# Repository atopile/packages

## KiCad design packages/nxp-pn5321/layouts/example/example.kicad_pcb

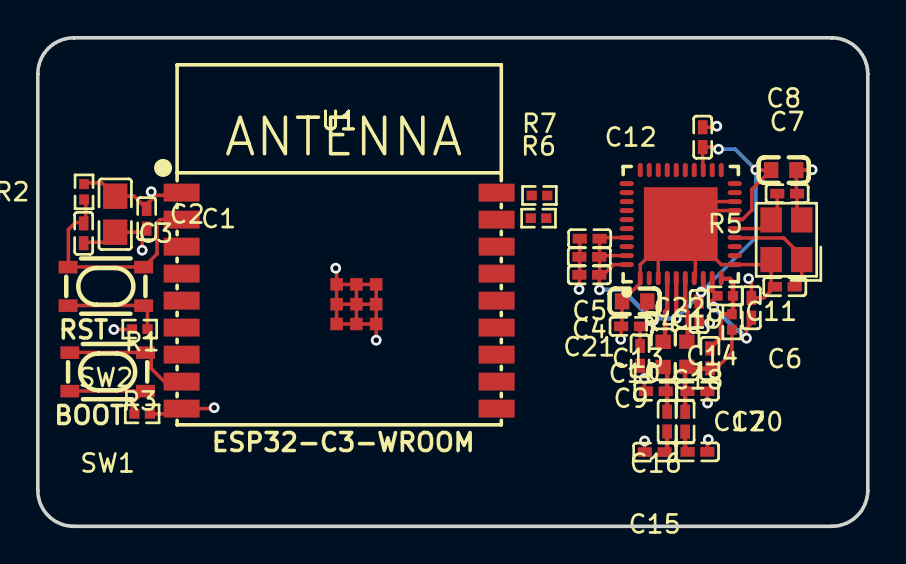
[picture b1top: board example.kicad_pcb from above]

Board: 2 copper layers, 46.1 x 27.1 mm, 36 parts (0 on the bottom side), 19 nets.

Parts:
C1, C4, C5, C9, C11, C12, C13, C14, C17, C20, C21, C22: 100nF ±10% 16V X7R; C0402
C2: 10µF ±10% 16V X5R; C0805
C3: 1µF ±10% 25V X5R; C0402
C6, C7: 20pF ±5% 50V C0G; C0402
C8, C10: 10µF ±20% 6.3V X5R; C0603
C15, C18: 100pF ±5% 50V C0G; C0402
C16, C19: 220pF ±10% 50V X7R; C0402
L1, L2: IND-SMD_L1.6-W0.8-1
R1, R3: 100Ω ±1% 62.5mW; R0402
R2: 10kΩ ±1% 62.5mW; R0402
R4, R5: 1kΩ ±1% 62.5mW; R0402
R6, R7: 4.7kΩ ±1% 62.5mW; R0402
SW1, SW2: KEY-SMD_4P-L4.2-W3.2-P2.20-LS4.6
U1: BULETM-SMD_ESPRESSIF_ESP32-C3-WROOM-02-N4-4MB
U2: QFN-40_L6.0-W6.0-P0.50-BL-EP4.1
X1: CRYSTAL-SMD_4P-L3.2-W2.5-BL

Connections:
-line-0: C18.1, C20.2
-line-1: C15.1, C17.2
MOSI_SDA_HSU_TX: R7.1, U1.18, U2.28
NSS_P50_SCL_HSU_RX: R6.1, U1.17, U2.27
RSTOUT_N: U1.10, U2.26
RX: C13.2, R4.2, R5.2, U2.10
TX1: L1.2, U2.4
TX2: L2.2, U2.6
VMID: C22.1, R5.1, U2.9
gnd: C1.2, C2.2, C3.2, C4.2, C5.2, C6.2, C7.2, C8.2, C9.2, C10.2, C11.2, C12.2, C14.2, C15.2, C16.2, C18.2, C19.2, C21.2, C22.2, R1.2, R3.2, U1.9, U1.19, U2.1, U2.3, U2.7, U2.11, U2.17, U2.18, U2.41, X1.2, X1.4
hv: C1.1, C2.1, C4.1, C5.1, C8.1, C9.1, C10.1, C11.1, C12.1, C14.1, C21.1, R2.2, R6.2, R7.2, U1.1, U2.5, U2.8, U2.16, U2.23, U2.37, U2.39, U2.40
input-0: R1.1, SW1.1, SW1.2
input-1: R3.1, SW2.1, SW2.2
nfc-input: C6.1, U2.14, X1.1
nfc-output: C7.1, U2.15, X1.3
output-0: SW1.3, SW1.4, U1.8
output-1: C3.1, R2.1, SW2.3, SW2.4, U1.2
tx_1_mid: C16.1, C17.1, L1.1
tx_2_mid: C13.1, C19.1, C20.1, L2.1, R4.1

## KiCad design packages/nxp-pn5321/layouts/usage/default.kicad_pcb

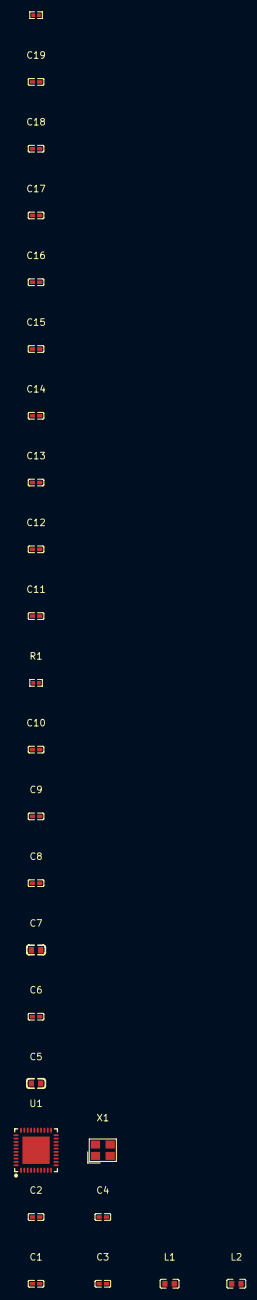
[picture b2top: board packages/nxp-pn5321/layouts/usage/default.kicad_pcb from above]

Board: 2 copper layers, 25 parts (0 on the bottom side), 12 nets.

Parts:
C1, C2, C6, C8, C9, C10, C11, C14, C17, C18, C19: 100nF ±10% 16V X7R; C0402
C3, C4: 20pF ±5% 50V C0G; C0402
C5, C7: 10µF ±20% 6.3V X5R; C0603
C12, C15: 100pF ±5% 50V C0G; C0402
C13, C16: 220pF ±10% 50V X7R; C0402
L1, L2: IND-SMD_L1.6-W0.8-1
R1, R2: 1kΩ ±1% 62.5mW; R0402
U1: QFN-40_L6.0-W6.0-P0.50-BL-EP4.1
X1: CRYSTAL-SMD_4P-L3.2-W2.5-BL

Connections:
-line-0: C15.1, C17.2
-line-1: C12.1, C14.2
RX: C10.2, R1.2, R2.2, U1.10
TX1: L1.2, U1.4
TX2: L2.2, U1.6
VMID: C19.1, R2.1, U1.9
gnd: C1.2, C2.2, C3.2, C4.2, C5.2, C6.2, C7.2, C8.2, C9.2, C11.2, C12.2, C13.2, C15.2, C16.2, C18.2, C19.2, U1.1, U1.3, U1.7, U1.11, U1.17, U1.18, U1.41, X1.2, X1.4
hv: C1.1, C2.1, C5.1, C6.1, C7.1, C8.1, C9.1, C11.1, C18.1, U1.5, U1.8, U1.16, U1.23, U1.37, U1.39, U1.40
input: C3.1, U1.14, X1.1
output: C4.1, U1.15, X1.3
tx_1_mid: C13.1, C14.1, L1.1
tx_2_mid: C10.1, C16.1, C17.1, L2.1, R1.1

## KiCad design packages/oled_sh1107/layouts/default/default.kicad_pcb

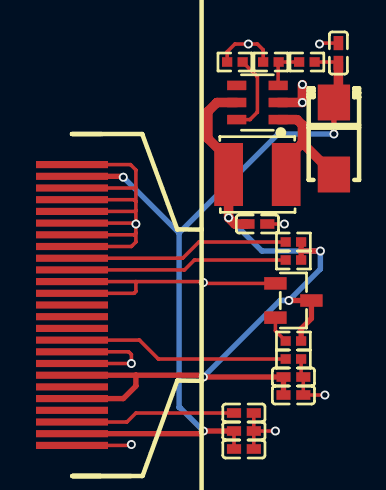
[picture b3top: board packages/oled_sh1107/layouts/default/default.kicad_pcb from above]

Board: 2 copper layers, 19 parts (0 on the bottom side), 11 nets.

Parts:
C1, C3, C7: 100nF ±10% 16V X7R; C0402
C2, C4: 4.7µF ±20% 16V X5R; C0402
C5: 2.2µF ±10% 16V X5R; C0402
C6: 10µF ±20% 6.3V X5R; C0402
D1: SMA_L4.2-W2.7-LS5.0-RD
L1: 10µH ±20% 1A 85mΩ; IND-SMD_L4.0-W4.0
OLED1: OLED-SMD_X150-2828KSWKG01-H25_1
R1: 910kΩ ±1% 62.5mW; R0402
R2, R3, R4, R7: 10kΩ ±1% 62.5mW; R0402
R5: 100kΩ ±1% 62.5mW; R0402
R6: 510Ω ±1% 62.5mW; R0402
U1: SOT-23-3_L2.9-W1.3-P1.90-LS2.4-BR
U2: SOT-23-6_L2.9-W1.6-P0.95-LS2.8-BL_3

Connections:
D0: OLED1.16, R2.1
D1: OLED1.17, R3.1
FB: R6.1, R7.2, U2.3
IREF: OLED1.10, R1.1
OC: R5.1, U2.6
VCC: C3.1, C4.1, C7.1, D1.1, OLED1.2, OLED1.24, R7.1
VCOMH: C5.1, OLED1.3
anode: D1.2, L1.2, U2.1
gnd: C1.2, C2.2, C3.2, C4.2, C5.2, C6.2, C7.2, OLED1.1, OLED1.8, OLED1.9, OLED1.14, OLED1.15, OLED1.18, OLED1.19, OLED1.20, OLED1.21, OLED1.22, OLED1.23, OLED1.25, R1.2, R5.2, R6.2, U1.1, U2.2
hv: C1.1, C2.1, C6.1, L1.1, OLED1.5, OLED1.7, R2.2, R3.2, R4.1, U1.3, U2.5
line: R4.2, U1.2

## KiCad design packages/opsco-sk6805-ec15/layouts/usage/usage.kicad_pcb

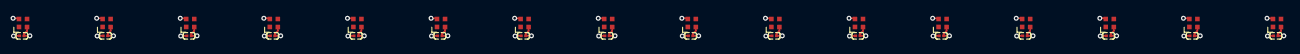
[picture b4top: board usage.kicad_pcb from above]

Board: 2 copper layers, 32 parts (0 on the bottom side), 17 nets.

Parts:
C1, C2, C3, C4, C5, C6, C7, C8, C9, C10, C11, C12, C13, C14, C15, C16: 100nF ±10%; C0201
LED1, LED2, LED3, LED4, LED5, LED6, LED7, LED8, LED9, LED10, LED11, LED12, LED13, LED14, LED15, LED16: LED-SMD_4P-L1.5-W1.5-BL

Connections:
data_out-DIN: LED10.3, LED11.1
hv: C1.1, C2.1, C3.1, C4.1, C5.1, C6.1, C7.1, C8.1, C9.1, C10.1, C11.1, C12.1, C13.1, C14.1, C15.1, C16.1, LED1.2, LED2.2, LED3.2, LED4.2, LED5.2, LED6.2, LED7.2, LED8.2, LED9.2, LED10.2, LED11.2, LED12.2, LED13.2, LED14.2, LED15.2, LED16.2
led_matrix[1]-data_in-DIN: LED1.3, LED2.1
led_matrix[2]-data_in-DIN: LED2.3, LED3.1
led_matrix[3]-data_in-DIN: LED3.3, LED4.1
led_matrix[4]-data_in-DIN: LED4.3, LED5.1
led_matrix[5]-data_in-DIN: LED5.3, LED6.1
led_matrix[6]-data_in-DIN: LED6.3, LED7.1
led_matrix[7]-data_in-DIN: LED7.3, LED8.1
led_matrix[8]-data_in-DIN: LED8.3, LED9.1
led_matrix[9]-data_in-DIN: LED9.3, LED10.1
led_matrix[11]-data_in-DIN: LED11.3, LED12.1
led_matrix[12]-data_in-DIN: LED12.3, LED13.1
led_matrix[13]-data_in-DIN: LED13.3, LED14.1
led_matrix[14]-data_in-DIN: LED14.3, LED15.1
led_matrix[15]-data_in-DIN: LED15.3, LED16.1
lv: C1.2, C2.2, C3.2, C4.2, C5.2, C6.2, C7.2, C8.2, C9.2, C10.2, C11.2, C12.2, C13.2, C14.2, C15.2, C16.2, LED1.4, LED2.4, LED3.4, LED4.4, LED5.4, LED6.4, LED7.4, LED8.4, LED9.4, LED10.4, LED11.4, LED12.4, LED13.4, LED14.4, LED15.4, LED16.4
